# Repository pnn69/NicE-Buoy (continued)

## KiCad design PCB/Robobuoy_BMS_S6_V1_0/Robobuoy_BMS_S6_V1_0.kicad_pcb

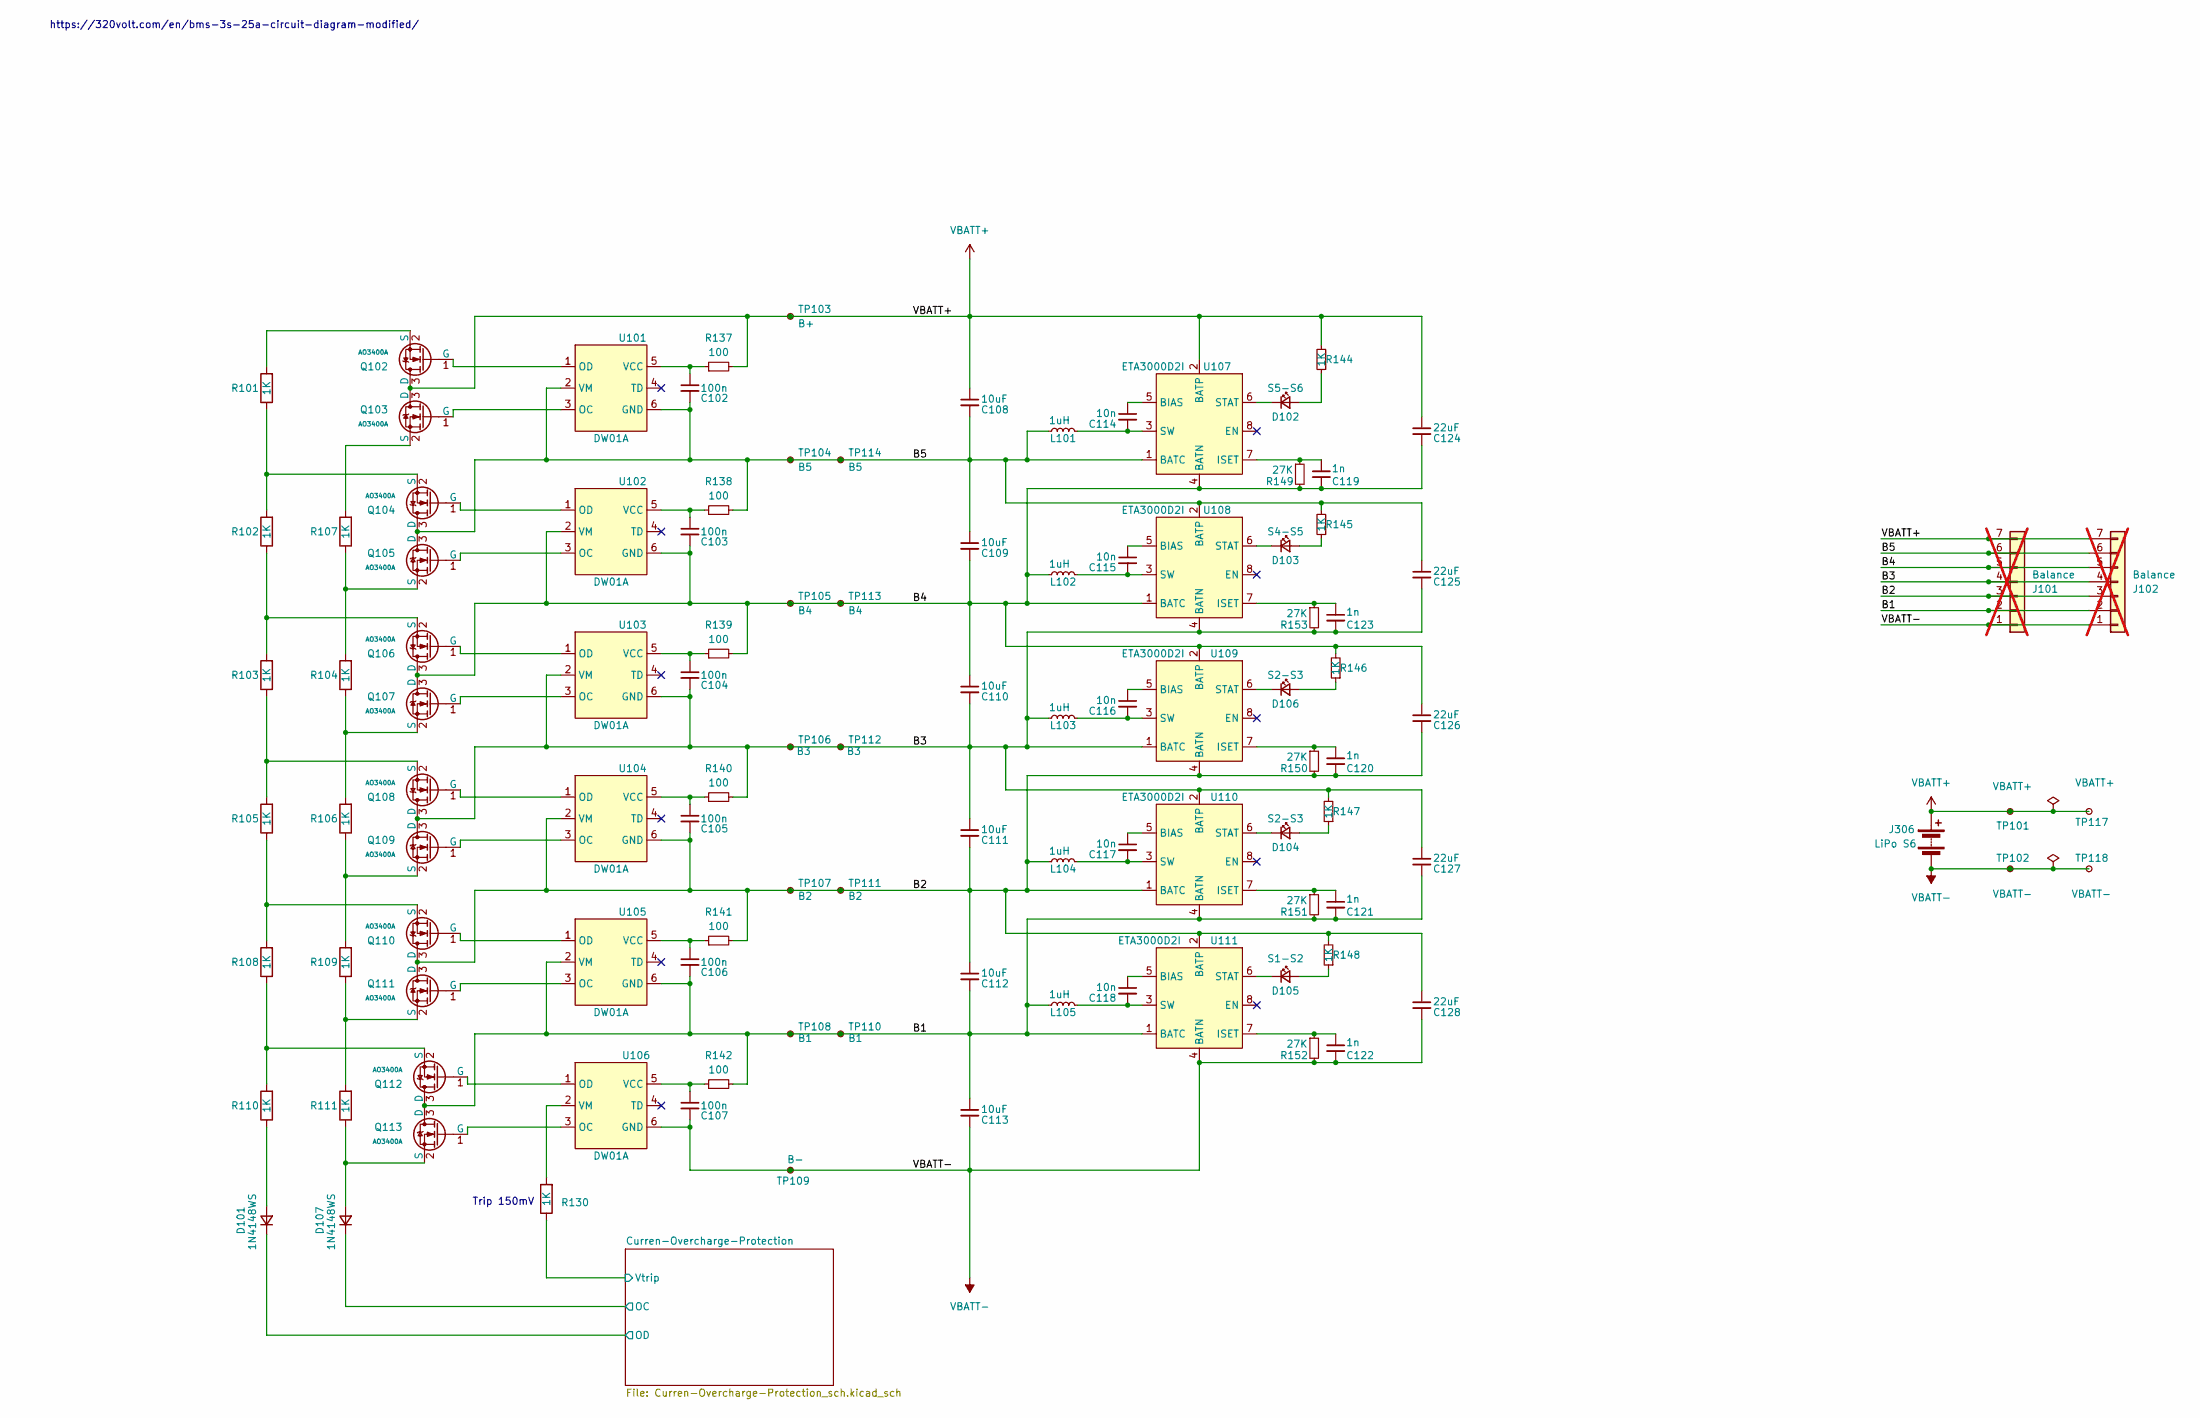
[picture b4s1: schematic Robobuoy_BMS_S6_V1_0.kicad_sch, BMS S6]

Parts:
C102, C103, C104, C105, C106, C107: 100n; C_0603; LCSC C14663
C108, C109, C110, C111, C112, C113: 10uF; C_0603; LCSC C96446
C114, C115, C116, C117, C118: 10n; C_0603; LCSC C57112
C119, C120, C121, C122, C123: 1n; C_0603; LCSC C1588
C124, C125, C126, C127, C128: 22uF; C_0805; LCSC C45783
D101, D107: 1N4148WS; D_SOD-323_1.8x1.4x1.15; LCSC C2128
D102, D103, D104, D105, D106: RED; LED_0603; LCSC C2286
J101, J102: Balance; JST_XH_B7B-XH-A_1x07_P2.50mm_Vertical; LCSC C144398; not fitted
J306: LiPo S6
L101, L102, L103, L104, L105: 1uH; L_6.6x7.0mm; LCSC C167216
Q102, Q103, Q104, Q105, Q106, Q107, Q108, Q109, Q110, Q111, Q112, Q113: AO3400A; Q_SOT-23; Part AO3400A; LCSC C20917
R101, R102, R103, R104, R105, R106, R107, R108, R109, R110, R111, R130, R144, R145, R146, R147, R148: 1K; R_0603; LCSC C21190
R137, R138, R139, R140, R141, R142: 100; R_0603; LCSC C22775
R149, R150, R151, R152, R153: 27K; R_0603; LCSC C23352
TP101, TP117: VBATT+; TestPad_7x8
TP102, TP118: VBATT-; TestPad_7x8
TP103: B+; TestPad_7x8
TP104, TP114: B5; TestPad_4x6
TP105, TP113: B4; TestPad_4x6
TP106, TP112: B3; TestPad_4x6
TP107, TP111: B2; TestPad_4x6
TP108, TP110: B1; TestPad_4x6
TP109: B-; TestPad_7x8
U101, U102, U103, U104, U105, U106: DW01A; SOT-23-6; LCSC C351410
U107, U108, U109, U110, U111: ETA3000D2I; DFN-8-1EP_2x2mm_P0.5mm_EP0.6x1.2mm; LCSC C7465544

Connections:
/B1: C106.2, C112.2, C113.1, C121.2, C127.2, J101.2, J102.2, L105.2, Q112.3 (D), Q113.3 (D), R142.2, R151.2, TP108.1, TP110.1, U105.2 (VM), U105.6 (GND), U110.4 (BATN), U110.9 (BATN), U111.1 (BATC)
/B2: C105.2, C111.2, C112.1, C120.2, C126.2, C128.1, J101.3, J102.3, L104.2, Q110.3 (D), Q111.3 (D), R141.2, R148.2, R150.2, TP107.1, TP111.1, U104.2 (VM), U104.6 (GND), U109.4 (BATN), U109.9 (BATN), U110.1 (BATC), U111.2 (BATP)
/B3: C104.2, C110.2, C111.1, C123.2, C125.2, C127.1, J101.4, J102.4, L103.2, Q108.3 (D), Q109.3 (D), R140.2, R147.2, R153.2, TP106.1, TP112.1, U103.2 (VM), U103.6 (GND), U108.4 (BATN), U108.9 (BATN), U109.1 (BATC), U110.2 (BATP)
/B4: C103.2, C109.2, C110.1, C119.2, C124.2, C126.1, J101.5, J102.5, L102.2, Q106.3 (D), Q107.3 (D), R139.2, R146.2, R149.2, TP105.1, TP113.1, U102.2 (VM), U102.6 (GND), U107.4 (BATN), U107.9 (BATN), U108.1 (BATC), U109.2 (BATP)
/B5: C102.2, C108.2, C109.1, C125.1, J101.6, J102.6, L101.2, Q104.3 (D), Q105.3 (D), R138.2, R145.2, TP104.1, TP114.1, U101.2 (VM), U101.6 (GND), U107.1 (BATC), U108.2 (BATP)
/Curren-Overcharge-Protection/OC: D107.1 (K); also elsewhere on the board
/Curren-Overcharge-Protection/OD: D101.1 (K); also elsewhere on the board
/Curren-Overcharge-Protection/Vtrip: R130.1; also elsewhere on the board
unnamed: D101.2 (A), R110.1
unnamed: D102.2 (A), R144.1
unnamed: D102.1 (K), U107.6 (STAT)
unnamed: D103.2 (A), R145.1
unnamed: D103.1 (K), U108.6 (STAT)
unnamed: D104.2 (A), R147.1
unnamed: D104.1 (K), U110.6 (STAT)
unnamed: D105.2 (A), R148.1
unnamed: D105.1 (K), U111.6 (STAT)
unnamed: D106.2 (A), R146.1
unnamed: D106.1 (K), U109.6 (STAT)
unnamed: D107.2 (A), Q113.2 (S), R111.1
unnamed: Q102.1 (G), U101.1 (OD)
unnamed: Q102.2 (S), R101.2
unnamed: Q103.1 (G), U101.3 (OC)
unnamed: Q103.2 (S), R107.2
unnamed: Q104.1 (G), U102.1 (OD)
unnamed: Q104.2 (S), R101.1, R102.2
unnamed: Q105.1 (G), U102.3 (OC)
unnamed: Q105.2 (S), R104.2, R107.1
unnamed: Q106.1 (G), U103.1 (OD)
unnamed: Q106.2 (S), R102.1, R103.2
unnamed: Q107.1 (G), U103.3 (OC)
unnamed: Q107.2 (S), R104.1, R106.2
unnamed: Q108.1 (G), U104.1 (OD)
unnamed: Q108.2 (S), R103.1, R105.2
unnamed: Q109.1 (G), U104.3 (OC)
unnamed: Q109.2 (S), R106.1, R109.2
unnamed: Q110.1 (G), U105.1 (OD)
unnamed: Q110.2 (S), R105.1, R108.2
unnamed: Q111.1 (G), U105.3 (OC)
unnamed: Q111.2 (S), R109.1, R111.2
unnamed: Q112.1 (G), U106.1 (OD)
unnamed: Q112.2 (S), R108.1, R110.2
unnamed: Q113.1 (G), U106.3 (OC)
unnamed: C102.1, R137.1, U101.5 (VCC)
unnamed: C103.1, R138.1, U102.5 (VCC)
unnamed: C104.1, R139.1, U103.5 (VCC)
unnamed: C105.1, R140.1, U104.5 (VCC)
unnamed: C106.1, R141.1, U105.5 (VCC)
unnamed: C107.1, R142.1, U106.5 (VCC)
unnamed: R130.2, U106.2 (VM)
unnamed: C114.1, U107.5 (BIAS)
unnamed: C119.1, R149.1, U107.7 (ISET)
unnamed: C114.2, L101.1, U107.3 (SW)
unnamed: C115.1, U108.5 (BIAS)
unnamed: C123.1, R153.1, U108.7 (ISET)
unnamed: C115.2, L102.1, U108.3 (SW)
unnamed: C116.1, U109.5 (BIAS)
unnamed: C120.1, R150.1, U109.7 (ISET)
unnamed: C116.2, L103.1, U109.3 (SW)
unnamed: C117.1, U110.5 (BIAS)
unnamed: C121.1, R151.1, U110.7 (ISET)
unnamed: C117.2, L104.1, U110.3 (SW)
unnamed: C118.1, U111.5 (BIAS)
unnamed: C122.1, R152.1, U111.7 (ISET)
unnamed: C118.2, L105.1, U111.3 (SW)
VBATT+: C108.1, C124.1, J101.7, J102.7, J306.2 (+), Q102.3 (D), Q103.3 (D), R137.2, R144.2, TP101.1, TP103.1, TP117.1, U107.2 (BATP); also elsewhere on the board
VBATT-: C107.2, C113.2, C122.2, C128.2, J101.1, J102.1, J306.1 (-), R152.2, TP102.1, TP109.1, TP118.1, U106.6 (GND), U111.4 (BATN), U111.9 (BATN); also elsewhere on the board

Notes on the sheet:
Trip 150mV
https://320volt.com/en/bms-3s-25a-circuit-diagram-modified/

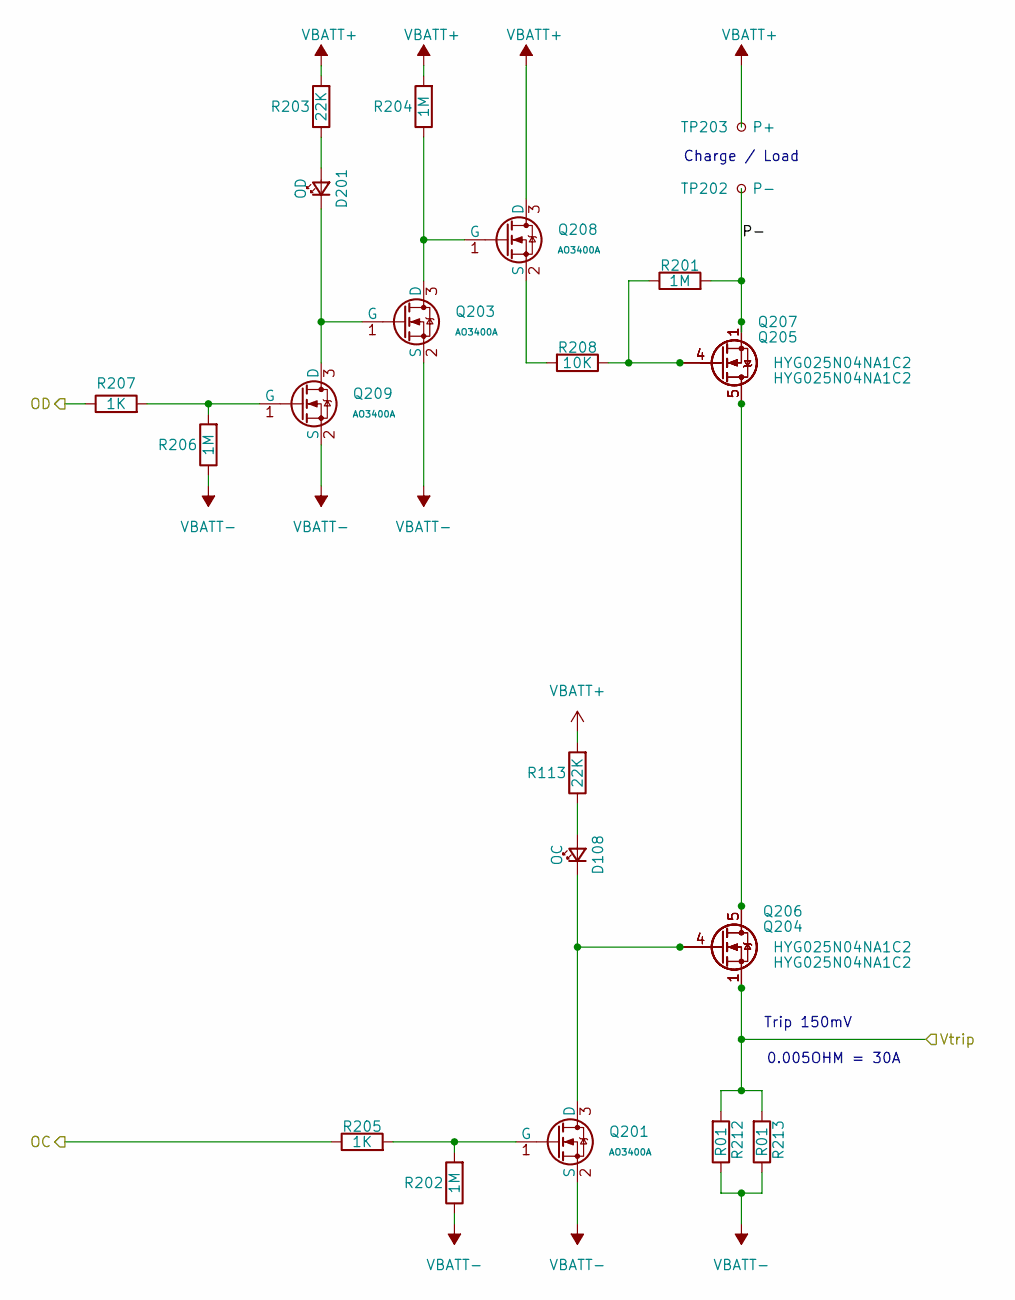
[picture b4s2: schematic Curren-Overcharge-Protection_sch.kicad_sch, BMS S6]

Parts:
D108, D201: RED; LED_0603; LCSC C2286
Q201, Q203, Q208, Q209: AO3400A; Q_SOT-23; Part AO3400A; LCSC C20917
Q204, Q205, Q206, Q207: HYG025N04NA1C2; PQFN-8-EP_6x5mm_P1.27mm_Generic; LCSC C2917677
R113, R203: 22K; R_0603; LCSC C31850
R201, R202, R204, R206: 1M; R_0603; LCSC C22935
R205, R207: 1K; R_0603; LCSC C21190
R208: 10K; R_0603
R212, R213: R01; R_2512_6332Metric_Pad1.40x3.35mm_HandSolder; LCSC C3013385
TP202: P-; TestPad_7x8
TP203: P+; TestPad_7x8

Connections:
/Curren-Overcharge-Protection/OC: R205.1; also elsewhere on the board
/Curren-Overcharge-Protection/OD: R207.1; also elsewhere on the board
/Curren-Overcharge-Protection/P-: Q205.1 (S), Q205.2 (S), Q205.3 (S), Q207.1 (S), Q207.2 (S), Q207.3 (S), R201.2, TP202.1
/Curren-Overcharge-Protection/Vtrip: Q204.1 (S), Q204.2 (S), Q204.3 (S), Q206.1 (S), Q206.2 (S), Q206.3 (S), R212.2, R213.2; also elsewhere on the board
unnamed: D108.2 (A), R113.1
unnamed: D108.1 (K), Q201.3 (D), Q204.4 (G), Q206.4 (G)
unnamed: D201.2 (A), R203.1
unnamed: D201.1 (K), Q203.1 (G), Q209.3 (D)
unnamed: Q201.1 (G), R202.2, R205.2
unnamed: Q203.3 (D), Q208.1 (G), R204.1
unnamed: Q204.5 (D), Q205.5 (D), Q206.5 (D), Q207.5 (D)
unnamed: Q205.4 (G), Q207.4 (G), R201.1, R208.1
unnamed: Q208.2 (S), R208.2
unnamed: Q209.1 (G), R206.2, R207.2
VBATT+: Q208.3 (D), R113.2, R203.2, R204.2, TP203.1; also elsewhere on the board
VBATT-: Q201.2 (S), Q203.2 (S), Q209.2 (S), R202.1, R206.1, R212.1, R213.1; also elsewhere on the board

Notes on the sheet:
0.005OHM = 30A
Charge / Load
Trip 150mV

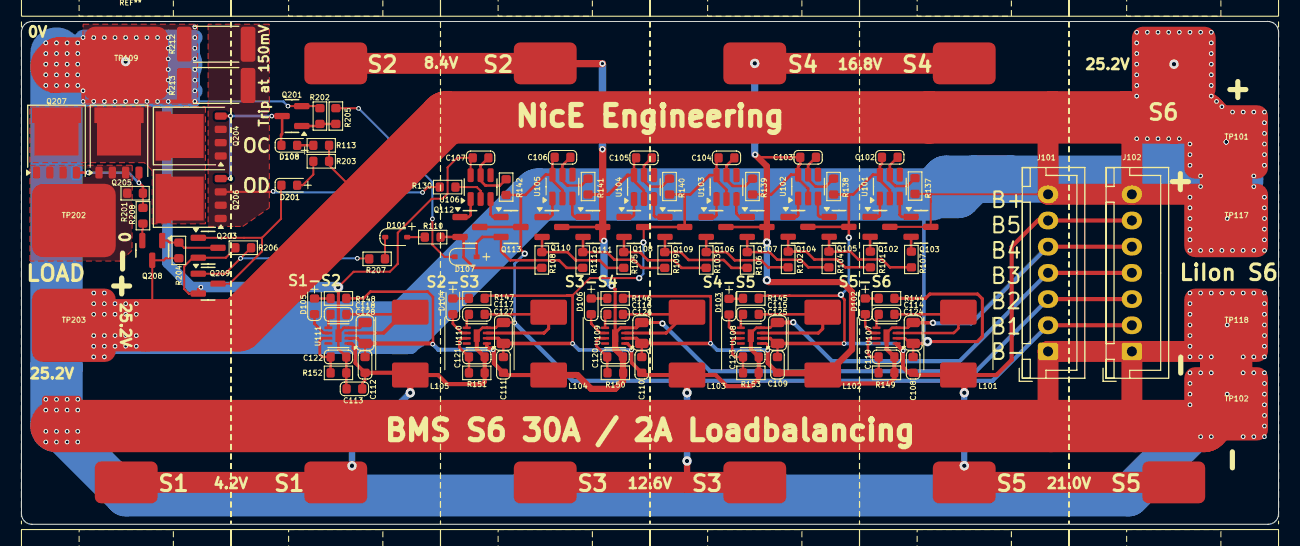
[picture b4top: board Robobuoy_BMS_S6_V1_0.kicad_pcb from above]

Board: 4 copper layers, 120.0 x 48.0 mm, 131 parts (0 on the bottom side), 78 nets.

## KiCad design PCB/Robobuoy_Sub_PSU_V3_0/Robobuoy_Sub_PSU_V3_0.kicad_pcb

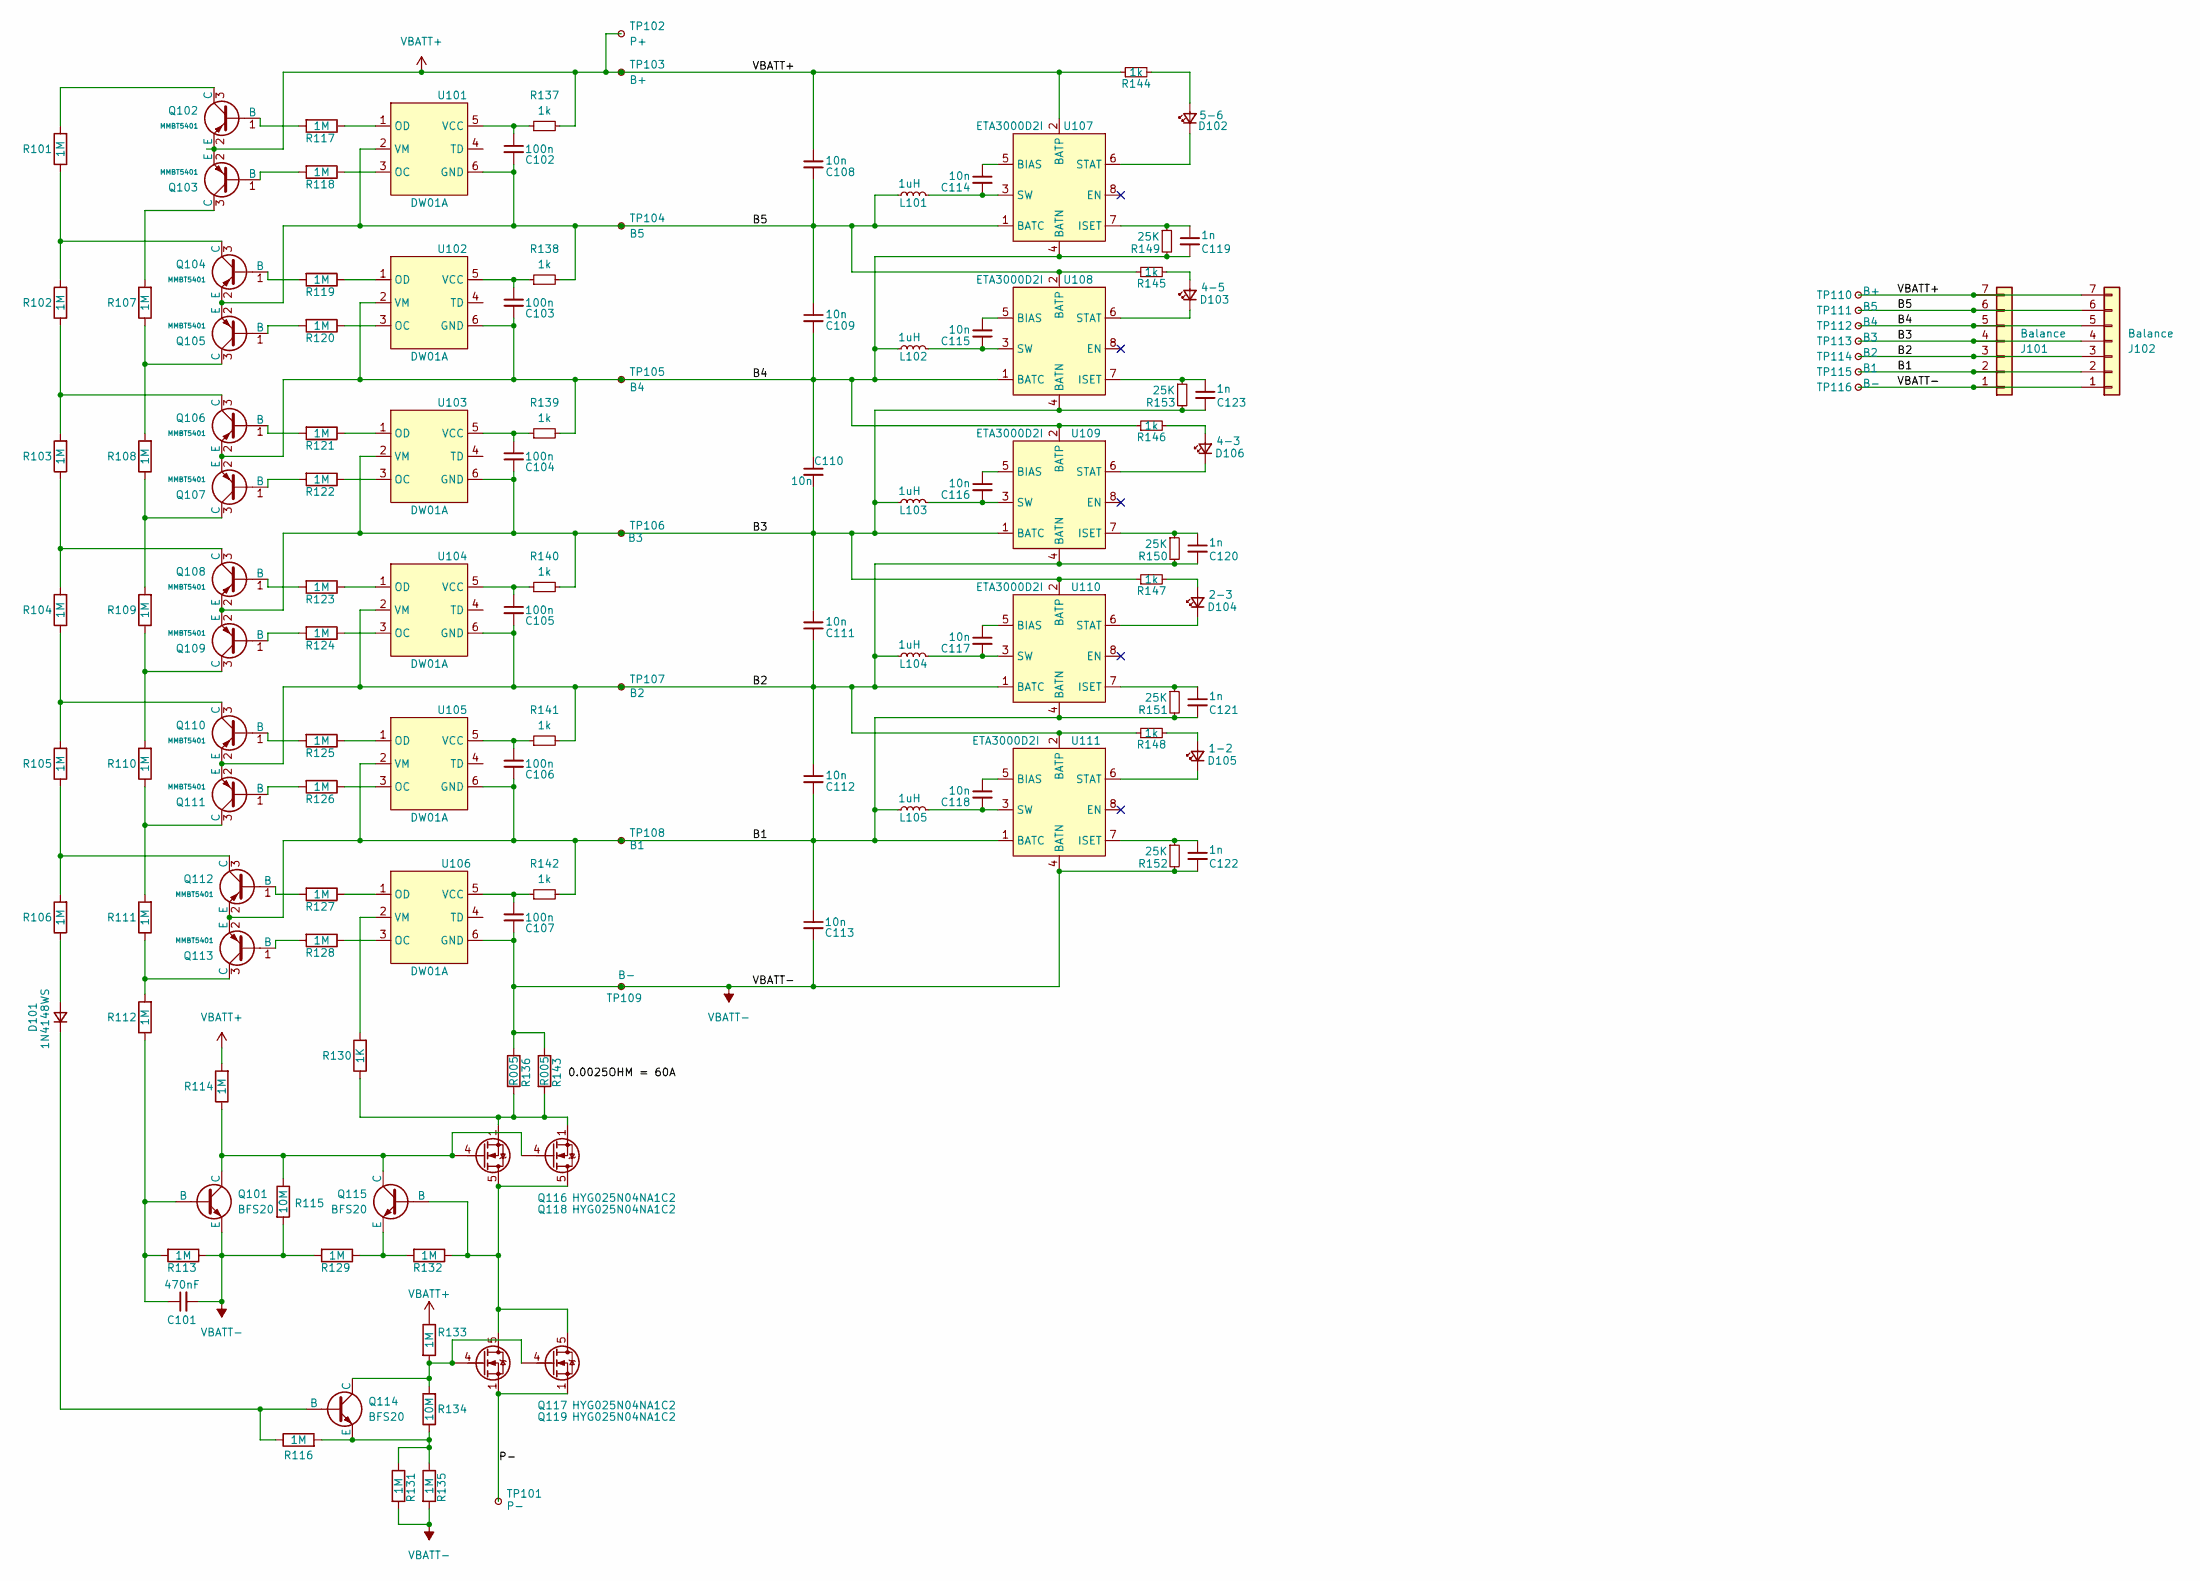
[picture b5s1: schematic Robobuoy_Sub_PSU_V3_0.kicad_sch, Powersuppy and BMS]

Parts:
C101: 470nF; C_0603; LCSC C1623
C102, C103, C104, C105, C106, C107: 100n; C_0603; LCSC C14663
C108, C109, C110, C111, C112, C113: 10n; C_0603; LCSC C57112
C114, C115, C116, C117, C118: 10n; C_0603; LCSC C1589
C119, C120, C121, C122, C123: 1n; C_0603; LCSC C1588
D101: 1N4148WS; D_SOD-323_1.8x1.4x1.15; LCSC C2128
D102: 5-6; LED_0805; LCSC C2297
D103: 4-5; LED_0805; LCSC C2297
D104: 2-3; LED_0805; LCSC C2297
D105: 1-2; LED_0805; LCSC C2297
D106: 4-3; LED_0805; LCSC C2297
J101, J102: Balance; JST_XH_B7B-XH-A_1x07_P2.50mm_Vertical; LCSC C144398
L101, L102, L103, L104, L105: 1uH; L_6.6x7.0mm; LCSC C167216
Q101, Q114, Q115: BFS20; SOT-23_jlc; LCSC C73088
Q102, Q103, Q104, Q105, Q106, Q107, Q108, Q109, Q110, Q111, Q112, Q113: MMBT5401; Q_SOT-23; Part MMBT5401; LCSC C7420356
Q116, Q117, Q118, Q119: HYG025N04NA1C2; PQFN-8-EP_6x5mm_P1.27mm_Generic; LCSC C2917677
R101, R102, R103, R104, R105, R106, R107, R108, R109, R110, R111, R112, R113, R114, R116, R117, R118, R119, R120, R121, R122, R123, R124, R125, R126, R127, R128, R129, R131, R132, R133, R135: 1M; R_0603; LCSC C22935
R115, R134: 10M; R_0603; LCSC C114606
R130: 1K; R_0603; LCSC C21190
R136, R143: R005; R_2512_6332Metric_Pad1.40x3.35mm_HandSolder; LCSC C185817
R137, R138, R139, R140, R141, R142, R144, R145, R146, R147, R148: 1k; R_0603; LCSC C21190
R149, R150, R151, R152, R153: 25K; R_0603
TP101: P-; TestPad_7x8
TP102: P+; TestPad_7x8
TP103: B+; TestPad_7x8
TP104: B5; TestPad_4x6
TP105: B4; TestPad_4x6
TP106: B3; TestPad_4x6
TP107: B2; TestPad_4x6
TP108: B1; TestPad_4x6
TP109: B-; TestPad_7x8
TP110: B+; TestPoint_Pad_D1.5mm
TP111: B5; TestPoint_Pad_D1.5mm
TP112: B4; TestPoint_Pad_D1.5mm
TP113: B3; TestPoint_Pad_D1.5mm
TP114: B2; TestPoint_Pad_D1.5mm
TP115: B1; TestPoint_Pad_D1.5mm
TP116: B-; TestPoint_Pad_D1.5mm
U101, U102, U103, U104, U105, U106: DW01A; SOT-23-6; LCSC C351410
U107, U108, U109, U110, U111: ETA3000D2I; DFN-8-1EP_2x2mm_P0.5mm_EP0.6x1.2mm; LCSC C7465544

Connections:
/B1: C106.2, C112.2, C113.1, C121.2, J101.2, J102.2, L105.2, Q112.2 (E), Q113.2 (E), R142.2, R151.2, TP108.1, TP115.1, U105.2 (VM), U105.6 (GND), U110.4 (BATN), U111.1 (BATC)
/B2: C105.2, C111.2, C112.1, C120.2, J101.3, J102.3, L104.2, Q110.2 (E), Q111.2 (E), R141.2, R148.1, R150.2, TP107.1, TP114.1, U104.2 (VM), U104.6 (GND), U109.4 (BATN), U110.1 (BATC), U111.2 (BATP)
/B3: C104.2, C110.2, C111.1, C123.2, J101.4, J102.4, L103.2, Q108.2 (E), Q109.2 (E), R140.2, R147.1, R153.2, TP106.1, TP113.1, U103.2 (VM), U103.6 (GND), U108.4 (BATN), U109.1 (BATC), U110.2 (BATP)
/B4: C103.2, C109.2, C110.1, C119.2, J101.5, J102.5, L102.2, Q106.2 (E), Q107.2 (E), R139.2, R146.1, R149.2, TP105.1, TP112.1, U102.2 (VM), U102.6 (GND), U107.4 (BATN), U108.1 (BATC), U109.2 (BATP)
/B5: C102.2, C108.2, C109.1, J101.6, J102.6, L101.2, Q104.2 (E), Q105.2 (E), R138.2, R145.1, TP104.1, TP111.1, U101.2 (VM), U101.6 (GND), U107.1 (BATC), U108.2 (BATP)
/P-: Q117.1 (S), Q117.2 (S), Q117.3 (S), Q119.1 (S), Q119.2 (S), Q119.3 (S), TP101.1
unnamed: D101.2 (A), R106.1
unnamed: D101.1 (K), Q114.1 (B), R116.1
unnamed: D102.2 (A), R144.2
unnamed: D102.1 (K), U107.6 (STAT)
unnamed: D103.2 (A), R145.2
unnamed: D103.1 (K), U108.6 (STAT)
unnamed: D104.2 (A), R147.2
unnamed: D104.1 (K), U110.6 (STAT)
unnamed: D105.2 (A), R148.2
unnamed: D105.1 (K), U111.6 (STAT)
unnamed: D106.2 (A), R146.2
unnamed: D106.1 (K), U109.6 (STAT)
unnamed: C101.1, Q101.1 (B), R112.1, R113.2
unnamed: Q101.3 (C), Q115.3 (C), Q116.4 (G), Q118.4 (G), R114.1, R115.1
unnamed: Q102.1 (B), R117.2
unnamed: Q102.3 (C), R101.2
unnamed: Q103.1 (B), R118.2
unnamed: Q103.3 (C), R107.2
unnamed: Q104.1 (B), R119.2
unnamed: Q104.3 (C), R101.1, R102.2
unnamed: Q105.1 (B), R120.2
unnamed: Q105.3 (C), R107.1, R108.2
unnamed: Q106.1 (B), R121.2
unnamed: Q106.3 (C), R102.1, R103.2
unnamed: Q107.1 (B), R122.2
unnamed: Q107.3 (C), R108.1, R109.2
unnamed: Q108.1 (B), R123.2
unnamed: Q108.3 (C), R103.1, R104.2
unnamed: Q109.1 (B), R124.2
unnamed: Q109.3 (C), R109.1, R110.2
unnamed: Q110.1 (B), R125.2
unnamed: Q110.3 (C), R104.1, R105.2
unnamed: Q111.1 (B), R126.2
unnamed: Q111.3 (C), R110.1, R111.2
unnamed: Q112.1 (B), R127.2
unnamed: Q112.3 (C), R105.1, R106.2
unnamed: Q113.1 (B), R128.2
unnamed: Q113.3 (C), R111.1, R112.2
unnamed: Q114.3 (C), Q117.4 (G), Q119.4 (G), R133.2, R134.2
unnamed: Q114.2 (E), R116.2, R131.1, R134.1, R135.1
unnamed: Q115.1 (B), Q116.5 (D), Q117.5 (D), Q118.5 (D), Q119.5 (D), R132.1
unnamed: Q115.2 (E), R129.1, R132.2
unnamed: Q116.1 (S), Q116.2 (S), Q116.3 (S), Q118.1 (S), Q118.2 (S), Q118.3 (S), R130.1, R136.2, R143.2
unnamed: R118.1, U101.3 (OC)
unnamed: R117.1, U101.1 (OD)
unnamed: C102.1, R137.1, U101.5 (VCC)
unnamed: R120.1, U102.3 (OC)
unnamed: R119.1, U102.1 (OD)
unnamed: C103.1, R138.1, U102.5 (VCC)
unnamed: R122.1, U103.3 (OC)
unnamed: R121.1, U103.1 (OD)
unnamed: C104.1, R139.1, U103.5 (VCC)
unnamed: R124.1, U104.3 (OC)
unnamed: R123.1, U104.1 (OD)
unnamed: C105.1, R140.1, U104.5 (VCC)
unnamed: R126.1, U105.3 (OC)
unnamed: R125.1, U105.1 (OD)
unnamed: C106.1, R141.1, U105.5 (VCC)
unnamed: R128.1, U106.3 (OC)
unnamed: R127.1, U106.1 (OD)
unnamed: C107.1, R142.1, U106.5 (VCC)
unnamed: R130.2, U106.2 (VM)
unnamed: C114.1, U107.5 (BIAS)
unnamed: C119.1, R149.1, U107.7 (ISET)
unnamed: C114.2, L101.1, U107.3 (SW)
unnamed: C115.1, U108.5 (BIAS)
unnamed: C123.1, R153.1, U108.7 (ISET)
unnamed: C115.2, L102.1, U108.3 (SW)
unnamed: C116.1, U109.5 (BIAS)
unnamed: C120.1, R150.1, U109.7 (ISET)
unnamed: C116.2, L103.1, U109.3 (SW)
unnamed: C117.1, U110.5 (BIAS)
unnamed: C121.1, R151.1, U110.7 (ISET)
unnamed: C117.2, L104.1, U110.3 (SW)
unnamed: C118.1, U111.5 (BIAS)
unnamed: C122.1, R152.1, U111.7 (ISET)
unnamed: C118.2, L105.1, U111.3 (SW)
VBATT+: C108.1, J101.7, J102.7, Q102.2 (E), Q103.2 (E), R114.2, R133.1, R137.2, R144.1, TP102.1, TP103.1, TP110.1, U107.2 (BATP)
VBATT-: C101.2, C107.2, C113.2, C122.2, J101.1, J102.1, Q101.2 (E), R113.1, R115.2, R129.2, R131.2, R135.2, R136.1, R143.1, R152.2, TP109.1, TP116.1, U106.6 (GND), U111.4 (BATN)

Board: 2 copper layers, 135 parts (0 on the bottom side), 85 nets, no tracks yet.

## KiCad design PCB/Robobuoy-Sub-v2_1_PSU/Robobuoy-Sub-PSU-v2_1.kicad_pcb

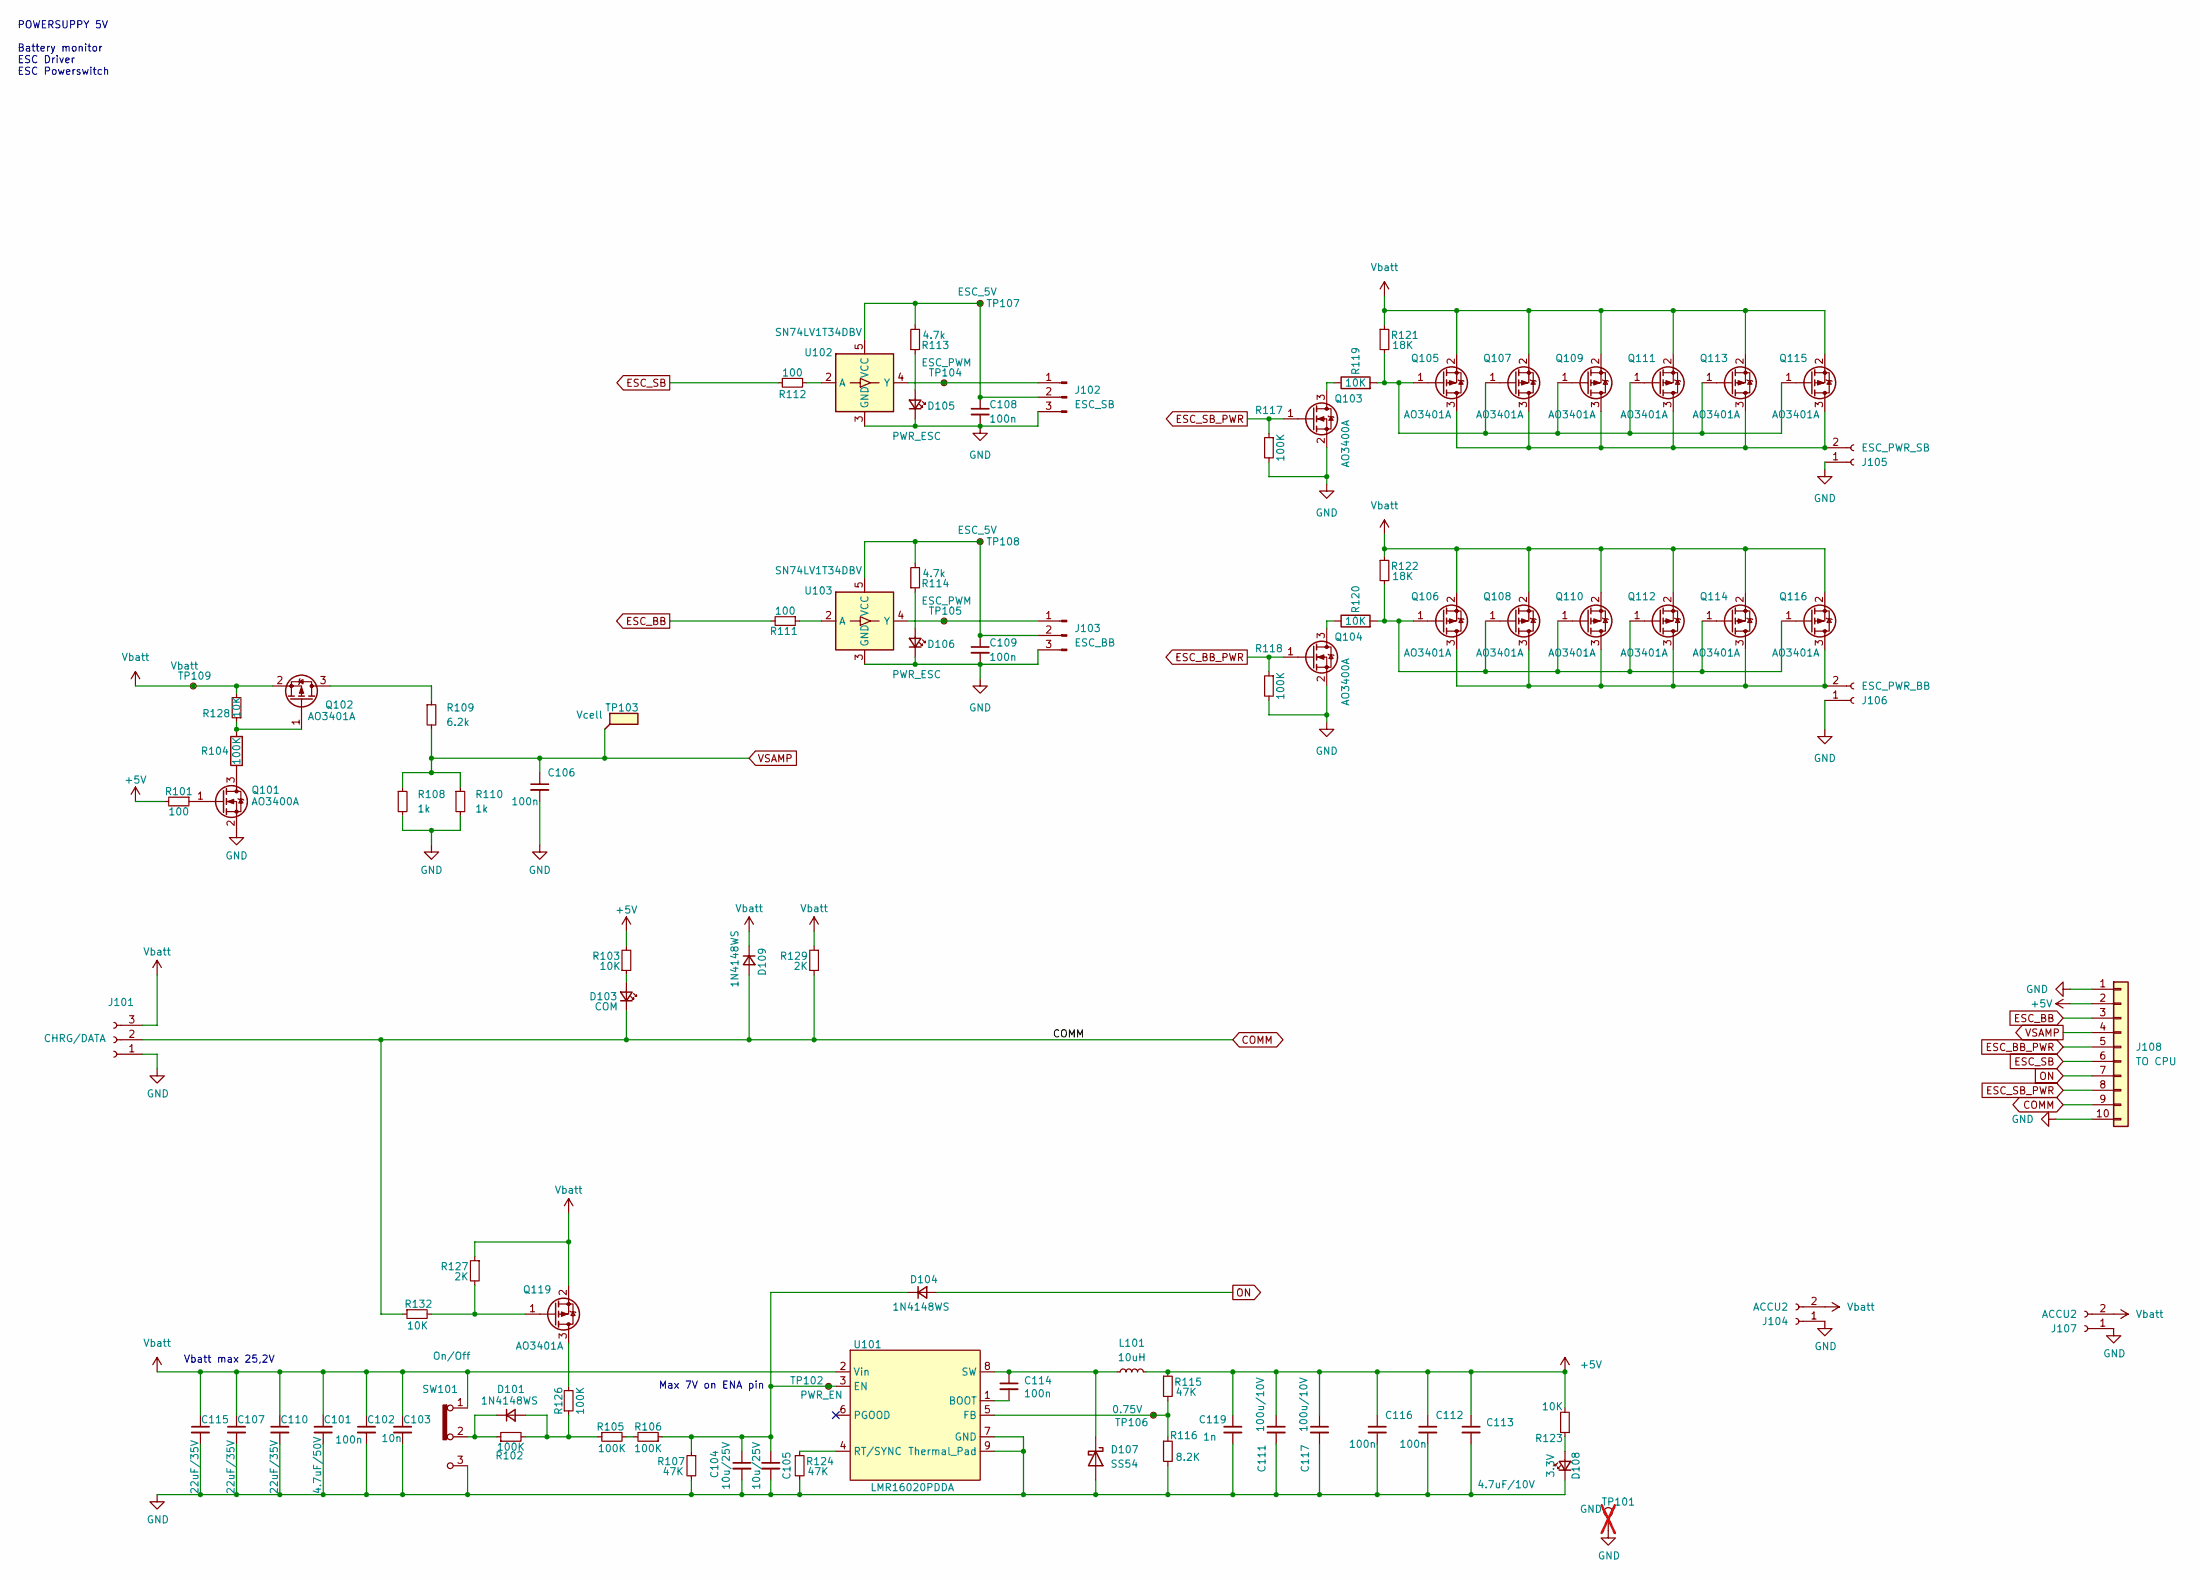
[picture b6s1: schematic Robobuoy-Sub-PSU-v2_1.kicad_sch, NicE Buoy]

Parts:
C101: 4.7uF/50V; C_1206_3216Metric; LCSC C29823
C102, C106, C108, C109, C112, C114, C116: 100n; C_0603; LCSC C14663
C103: 10n; C_0603; LCSC C57112
C104, C105: 10u/25V; C_0805; LCSC C15850
C107, C110, C115: 22uF/35V; C_1206_3216Metric; LCSC C6119969
C111, C117: 100u/10V; C_1210_3225Metric; LCSC C23742
C113: 4.7uF/10V; C_1206_3216Metric; LCSC C29823
C119: 1n; C_0603; LCSC C1588
D101, D104, D109: 1N4148WS; D_SOD-323_1.8x1.4x1.15; LCSC C2128
D103: COM; LED_0603_1608Metric; LCSC C2286
D105, D106: PWR_ESC; LED_0603_1608Metric; LCSC C2286
D107: SS54; D_SMA; LCSC C22452
D108: 3.3V; LED_0805; LCSC C2297
J101: CHRG/DATA; AMASS_XT60IPW-M_1x03_P5.50mm_Vertical; LCSC C19268044
J102: ESC_SB; JST_XH_B3B-XH-A_1x03_P2.50mm_Vertical; LCSC C5341202
J103: ESC_BB; JST_XH_B3B-XH-A_1x03_P2.50mm_Vertical; LCSC C5341202
J104, J107: ACCU2; AMASS_XT60IPW-M_1x03_P7.20mm_Horizontal; LCSC C98732
J105: ESC_PWR_SB; AMASS_XT60PW-F_1x02_P7.20mm_Horizontal; LCSC C428722
J106: ESC_PWR_BB; AMASS_XT60PW-F_1x02_P7.20mm_Horizontal; LCSC C428722
J108: TO CPU; IDC-Header_2x05_P2.54mm_Vertical; LCSC C5665
L101: 10uH; L_6.6x7.0mm; LCSC C2894722
Q101, Q103, Q104: AO3400A; SOT-23; LCSC C20917
Q102, Q105, Q106, Q107, Q108, Q109, Q110, Q111, Q112, Q113, Q114, Q115, Q116, Q119: AO3401A; SOT-23; LCSC C15127
R101, R111, R112: 100; R_0603; LCSC C22775
R102, R105, R106, R117, R118, R126: 100K; R_0603; LCSC C25804
R103, R123, R128, R132: 10K; R_0603; LCSC C25804
R104: 100K; R_0603; Farnell 2331736
R107, R115, R124: 47K; R_0603; LCSC C25819
R108, R110: 1k; R_0603; LCSC C21190
R109: 6.2k; R_0603; LCSC C25804
R113, R114: 4.7k; R_0603; LCSC C4177
R116: 8.2K; R_0603; LCSC C25981
R119, R120: 10K; R_0603; Farnell 2331736
R121, R122: 18K; R_0603; LCSC C25810
R127, R129: 2K; R_0603; LCSC C22975
SW101: On/Off; Header_1x03_P2.54_Male; LCSC C2937625
TP101: GND; TestPoint_Loop_D2.54mm_Drill1.5mm_Beaded; not fitted
TP102: PWR_EN; Testpad_1.4
TP103: Vcell; Testpad_1
TP104: ESC_PWM; Testpad_1
TP105: ESC_PWM; Testpad_1.4
TP106: 0.75V; Testpad_1.4
TP107: ESC_5V; Testpad_1
TP108: ESC_5V; Testpad_1.4
TP109: Vbatt; Testpad_1.4
U101: LMR16020PDDA; SOIC-8-1EP_3.9x4.9mm_P1.27mm_EP2.41x3.81mm_ThermalVias; LCSC C190006
U102, U103: SN74LV1T34DBV; SOT-23-5; LCSC C100024

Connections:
+5V: C111.1, C112.1, C113.1, C116.1, C117.1, C119.1, J108.2, L101.2, R101.2, R103.2, R115.1, R123.2
COMM: D103.1 (K), D109.2 (A), J101.2, J108.9, R129.2, R132.1
ESC_BB: J108.3, R111.2
ESC_BB_PWR: J108.5, Q104.1 (G), R118.1
ESC_SB: J108.6, R112.2
ESC_SB_PWR: J108.8, Q103.1 (G), R117.1
GND: C101.2, C102.2, C103.2, C104.2, C105.2, C106.2, C107.2, C108.2, C109.2, C110.2, C111.2, C112.2, C113.2, C115.2, C116.2, C117.2, C119.2, D105.1 (K), D106.1 (K), D107.2 (A), D108.1 (K), J101.1, J102.3, J103.3, J104.1, J105.1, J106.1, J107.1, J108.1, J108.10, Q101.2 (S), Q103.2 (S), Q104.2 (S), R107.2, R108.2, R110.2, R116.2, R117.2, R118.2, R124.2, SW101.3, TP101.1, U101.7 (GND), U101.9 (Thermal_Pad), U102.3 (GND), U103.3 (GND)
unnamed: D101.2 (A), R102.2, R105.1, R126.1
unnamed: D101.1 (K), R102.1, SW101.2
unnamed: D103.2 (A), R103.1
unnamed: C104.1, C105.1, D104.1 (K), R106.1, R107.1, TP102.1, U101.3 (EN)
unnamed: D105.2 (A), R113.1
unnamed: D106.2 (A), R114.1
unnamed: C114.1, D107.1 (K), L101.1, U101.8 (SW)
unnamed: D108.2 (A), R123.1
unnamed: J102.1, TP104.1, U102.4 (Y)
unnamed: C108.1, J102.2, R113.2, TP107.1, U102.5 (VCC)
unnamed: J103.1, TP105.1, U103.4 (Y)
unnamed: C109.1, J103.2, R114.2, TP108.1, U103.5 (VCC)
unnamed: J105.2, Q105.3 (D), Q107.3 (D), Q109.3 (D), Q111.3 (D), Q113.3 (D), Q115.3 (D)
unnamed: J106.2, Q106.3 (D), Q108.3 (D), Q110.3 (D), Q112.3 (D), Q114.3 (D), Q116.3 (D)
unnamed: Q101.3 (D), R104.1
unnamed: Q101.1 (G), R101.1
unnamed: Q102.3 (D), R109.1
unnamed: Q102.1 (G), R104.2, R128.1
unnamed: Q103.3 (D), R119.1
unnamed: Q104.3 (D), R120.1
unnamed: Q105.1 (G), Q107.1 (G), Q109.1 (G), Q111.1 (G), Q113.1 (G), Q115.1 (G), R119.2, R121.2
unnamed: Q106.1 (G), Q108.1 (G), Q110.1 (G), Q112.1 (G), Q114.1 (G), Q116.1 (G), R120.2, R122.2
unnamed: Q119.3 (D), R126.2
unnamed: Q119.1 (G), R127.2, R132.2
unnamed: R105.2, R106.2
unnamed: C114.2, U101.1 (BOOT)
unnamed: R115.2, R116.1, TP106.1, U101.5 (FB)
unnamed: R124.1, U101.4 (RT/SYNC)
unnamed: R112.1, U102.2 (A)
unnamed: R111.1, U103.2 (A)
ON: D104.2 (A), J108.7
VSAMP: C106.1, J108.4, R108.1, R109.2, R110.1, TP103.1
Vbatt: C101.1, C102.1, C103.1, C107.1, C110.1, C115.1, D109.1 (K), J101.3, J104.2, J107.2, Q102.2 (S), Q105.2 (S), Q106.2 (S), Q107.2 (S), Q108.2 (S), Q109.2 (S), Q110.2 (S), Q111.2 (S), Q112.2 (S), Q113.2 (S), Q114.2 (S), Q115.2 (S), Q116.2 (S), Q119.2 (S), R121.1, R122.1, R127.1, R128.2, R129.1, SW101.1, TP109.1, U101.2 (Vin)

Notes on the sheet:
Max 7V on ENA pin
POWERSUPPY 5V Battery monitor ESC Driver ESC Powerswitch
Vbatt max 25,2V
